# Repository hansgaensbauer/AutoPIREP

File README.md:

# AutoPIREP
AutoPIREP is a website, backend, and IOS app for automatically reporting turbulence in General Aviation flights. Traditionally, a pilot is expected to radio air traffic control to submit a Pilot Report (PIREP) when they encounter turbulence. The IOS app presented here uses the accelerometer in an iPhone to detect turbulence, and then submits reports to a custom backend running in AWS. The website displays the reports on a map for other pilots to reference.

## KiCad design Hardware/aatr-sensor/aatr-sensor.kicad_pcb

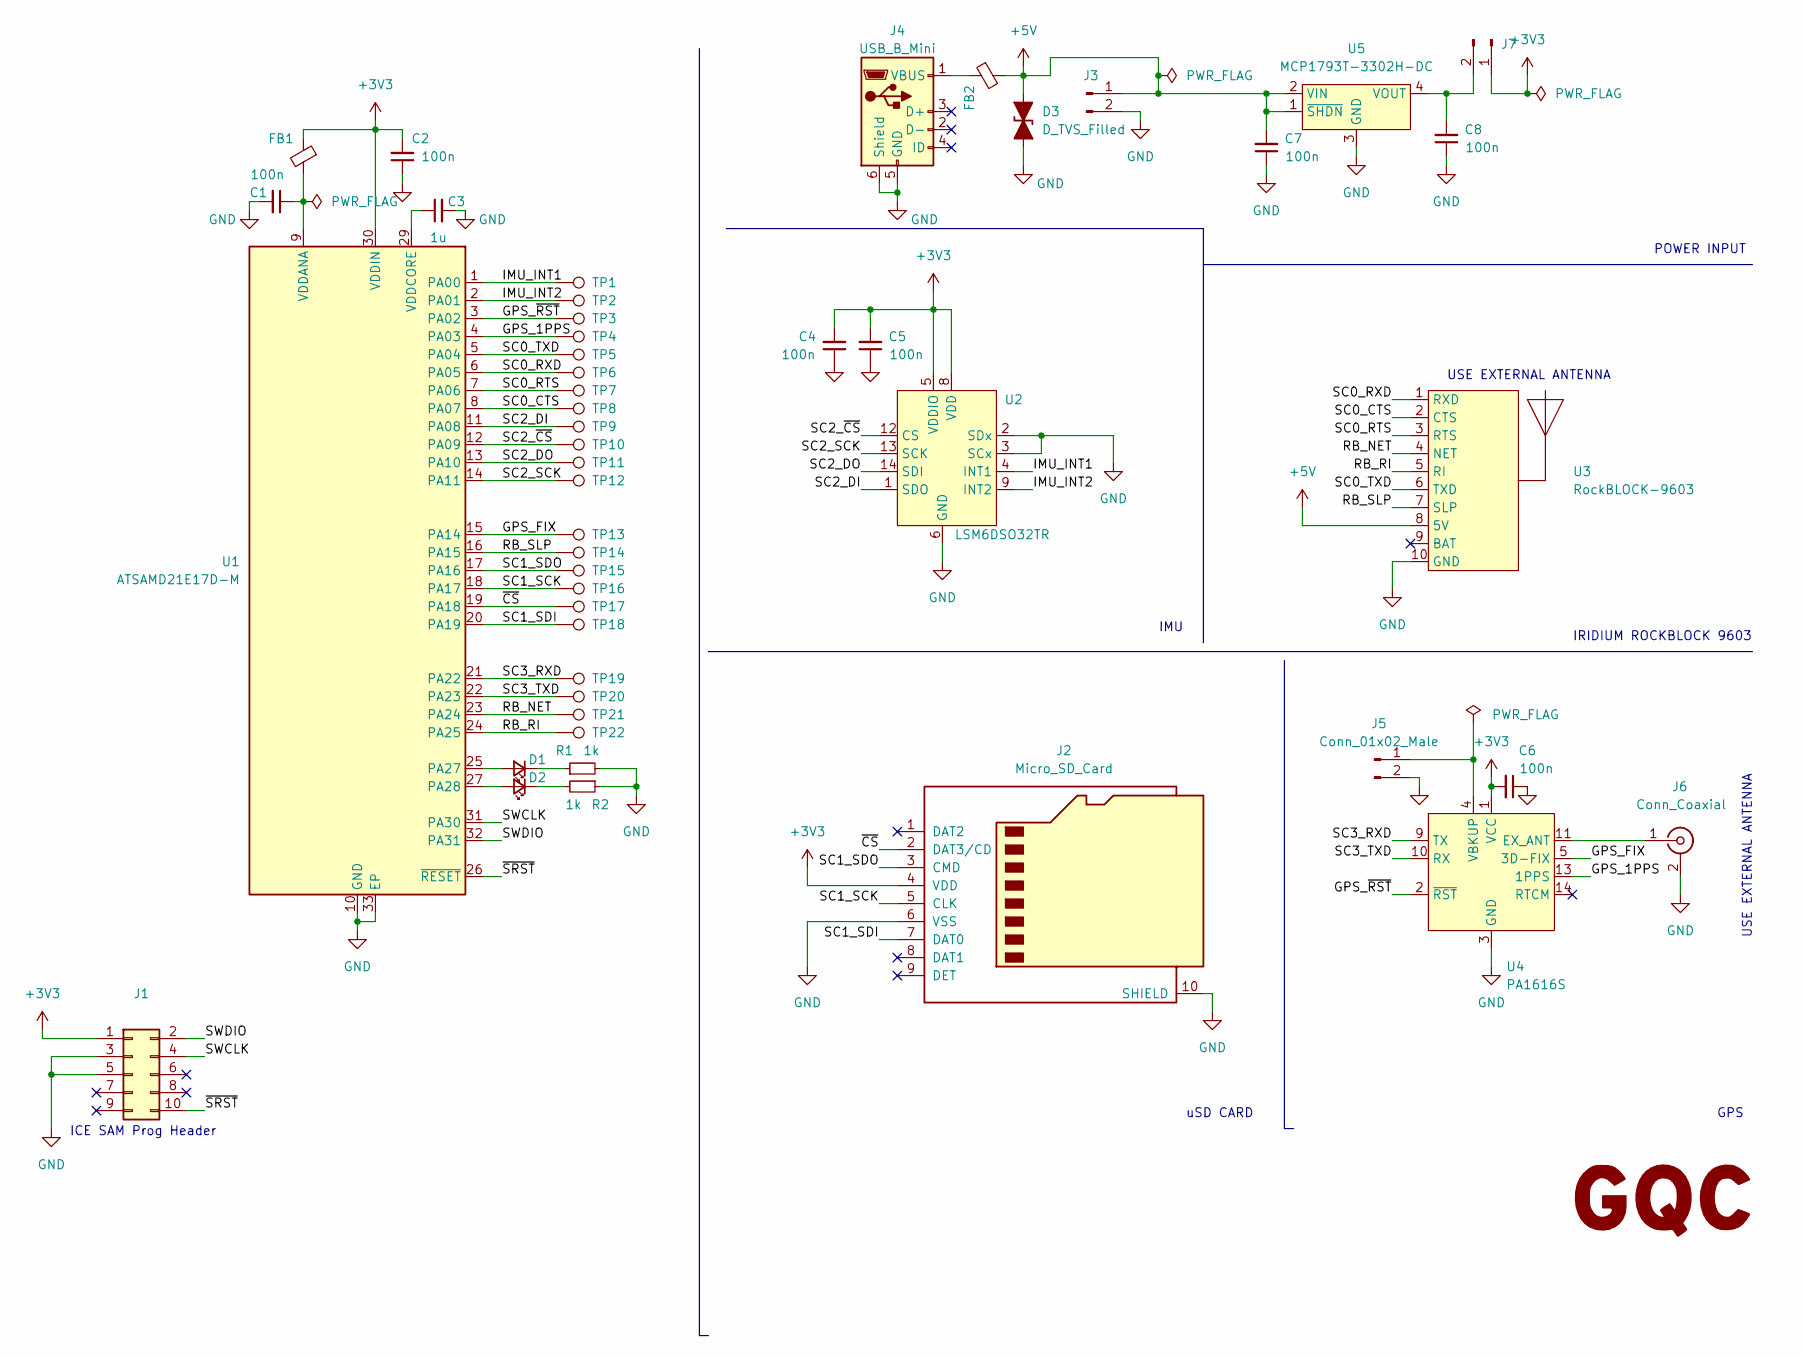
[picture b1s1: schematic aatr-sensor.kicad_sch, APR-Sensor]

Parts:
C1, C2, C4, C5, C6, C7, C8: 100n; C_0603_1608Metric
C3: 1u; C_0603_1608Metric
D1, D2: LED_Small; LED_0805_2012Metric
D3: D_TVS_Filled; D_0201_0603Metric
FB1, FB2: FerriteBead_Small; L_0603_1608Metric
G1: GQC-Logo
J1: Conn_02x05_Odd_Even; 3221-10-0300-00-TR
J2: Micro_SD_Card; MEM2051-00-195-00-A
J3, J5, J7: Conn_01x02_Male; PinHeader_1x02_P2.54mm_Vertical
J4: USB_B_Mini; USB_Mini-B_Wuerth_65100516121_Horizontal
J6: Conn_Coaxial; SMA_Samtec_SMA-J-P-X-ST-EM1_EdgeMount
R1, R2: 1k; R_0603_1608Metric
TP1, TP2, TP3, TP4, TP5, TP6, TP7, TP8, TP9, TP10, TP11, TP12, TP13, TP14, TP15, TP16, TP17, TP18, TP19, TP20, TP21, TP22: TestPoint; RCU-0603
U1: ATSAMD21E17D-M; QFN-32-1EP_5x5mm_P0.5mm_EP3.6x3.6mm
U2: LSM6DSO32TR; LGA-14_3x2.5mm_P0.5mm_LayoutBorder3x4y
U3: RockBLOCK-9603; Molex_PicoBlade_53047-1010_1x10_P1.25mm_Vertical
U4: PA1616S; FGPMMOPA6H
U5: MCP1793T-3302H-DC; SOT-223-6

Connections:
+3V3: C2.2, C4.2, C5.2, C6.2, FB1.1, J1.1, J2.4 (VDD), J7.1, U1.30 (VDDIN), U2.5 (VDDIO), U2.8 (VDD), U4.1 (VCC)
+5V: C7.2, D3.2 (A2), FB2.2, J3.1, U3.8 (5V), U5.1 (~SHDN), U5.2 (VIN)
/GPS_1PPS: TP4.1, U1.4 (PA03), U4.13 (1PPS)
/GPS_FIX: TP13.1, U1.15 (PA14), U4.5 (3D-FIX)
/GPS_~RST: TP3.1, U1.3 (PA02), U4.2 (~RST)
/IMU_INT1: TP1.1, U1.1 (PA00), U2.4 (INT1)
/IMU_INT2: TP2.1, U1.2 (PA01), U2.9 (INT2)
/RB_NET: TP21.1, U1.23 (PA24), U3.4 (NET)
/RB_RI: TP22.1, U1.24 (PA25), U3.5 (RI)
/RB_SLP: TP14.1, U1.16 (PA15), U3.7 (SLP)
/SC0_CTS: TP8.1, U1.8 (PA07), U3.2 (CTS)
/SC0_RTS: TP7.1, U1.7 (PA06), U3.3 (RTS)
/SC0_RXD: TP6.1, U1.6 (PA05), U3.1 (RXD)
/SC0_TXD: TP5.1, U1.5 (PA04), U3.6 (TXD)
/SC1_SCK: J2.5 (CLK), TP16.1, U1.18 (PA17)
/SC1_SDI: J2.7 (DAT0), TP18.1, U1.20 (PA19)
/SC1_SDO: J2.3 (CMD), TP15.1, U1.17 (PA16)
/SC2_DI: TP9.1, U1.11 (PA08), U2.1 (SDO)
/SC2_DO: TP11.1, U1.13 (PA10), U2.14 (SDI)
/SC2_SCK: TP12.1, U1.14 (PA11), U2.13 (SCK)
/SC2_~CS: TP10.1, U1.12 (PA09), U2.12 (CS)
/SC3_RXD: TP19.1, U1.21 (PA22), U4.9 (TX)
/SC3_TXD: TP20.1, U1.22 (PA23), U4.10 (RX)
/SWCLK: J1.4, U1.31 (PA30)
/SWDIO: J1.2, U1.32 (PA31)
/~CS: J2.2 (DAT3/CD), TP17.1, U1.19 (PA18)
/~SRST: J1.10, U1.26 (~RESET)
GND: C1.2, C2.1, C3.2, C4.1, C5.1, C6.1, C7.1, C8.1, D3.1 (A1), J1.3, J1.5, J2.6 (VSS), J2.10 (SHIELD), J3.2, J4.5 (GND), J4.6 (Shield), J5.2, J6.2 (Ext), R1.2, R2.1, U1.10 (GND), U1.28 (GND), U1.33 (EP), U2.2 (SDx), U2.3 (SCx), U2.6 (GND), U2.7 (GND), U3.10 (GND), U4. (GND), U4.3 (GND), U4.8 (GND), U4.12 (GND), U4.19 (GND), U5.3 (GND), U5.6 (GND)
unnamed: C1.1, FB1.2, U1.9 (VDDANA)
unnamed: C3.1, U1.29 (VDDCORE)
unnamed: C8.2, J7.2, U5.4 (VOUT)
unnamed: D1.1 (K), R1.1
unnamed: D1.2 (A), U1.25 (PA27)
unnamed: D2.1 (K), R2.2
unnamed: D2.2 (A), U1.27 (PA28)
unnamed: FB2.1, J4.1 (VBUS)
unnamed: J5.1, U4.4 (VBKUP)
unnamed: J6.1 (In), U4.11 (EX_ANT)

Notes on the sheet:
ICE SAM Prog Header
GPS
uSD CARD
IMU
USE EXTERNAL ANTENNA
IRIDIUM ROCKBLOCK 9603
POWER INPUT

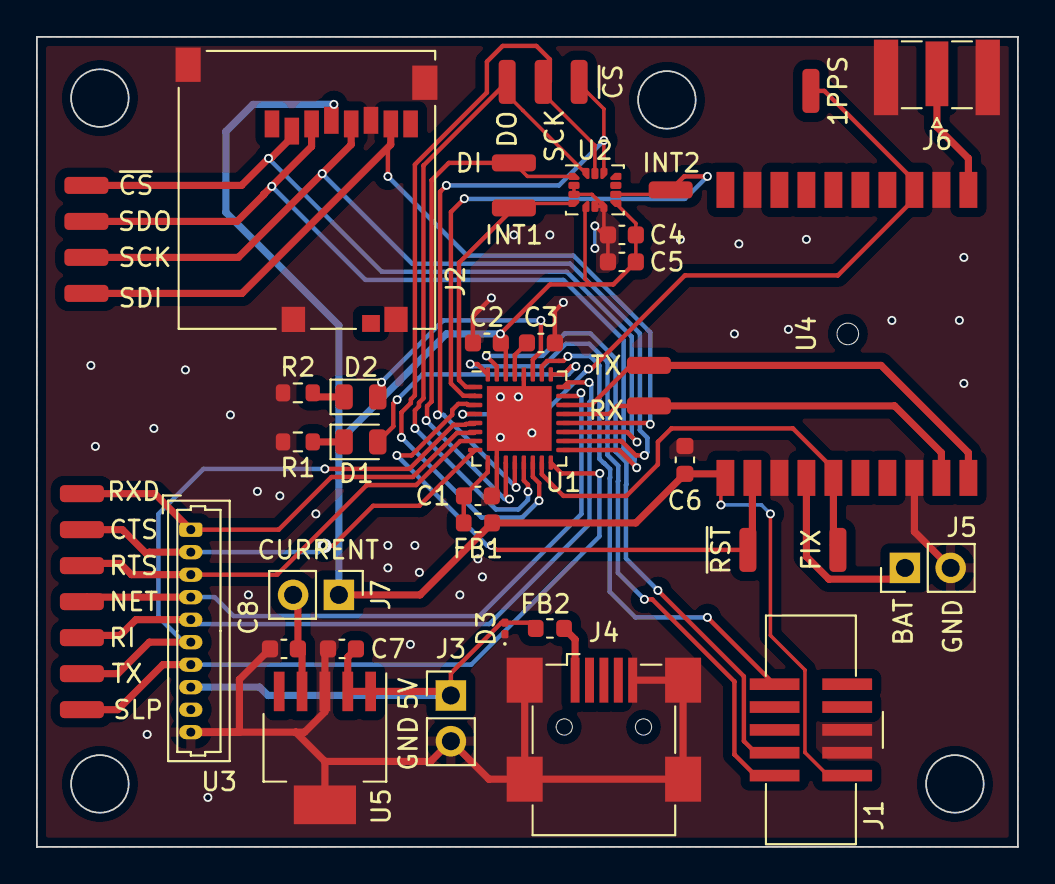
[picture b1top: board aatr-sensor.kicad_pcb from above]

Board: 2 copper layers, 54.5 x 45.0 mm, 50 parts (1 on the bottom side), 38 nets.

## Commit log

2022-05-03 Datalogger: Add firmware to remote
    Add the python files and bash scripts for setting up the RPi datalogger to the repo.
2022-05-23 APR-Sensor First Pass ERC Pass
2022-05-25 APR-Sensor Floorplanning
2022-05-26 AATR-Sensor: Create BOM, CAM Files
2022-05-26 AATR-Sensor: Remove Backups
2022-06-18 Update Science Names, add pdf Schematic
2022-06-18 Create Firmware Branch
    Created Microchip Studio project with ASF
2022-06-18 Add Documentation and AATR Image
2022-06-29 FW: ADD ASF Components
    Included SDMMC, FATFS, and delay drivers. Projects builds without errors.
2022-06-29 FW: SD log compiles
2022-06-29 FW: Added board init and error handlers
2022-07-03 FW: Debug SDMMC
2022-07-04 FW: Add UART Support
2022-07-06 FW: USART Works
2022-07-06 FW: Fix RX for USART
2022-07-06 FW: IMU SPI Driver Works
2022-07-06 FW: SPI Talks to IMU
2022-07-06 FW: SPI Debugging
2022-07-07 FW: Reading IMU Data
2022-07-07 FW: Fix IMU XL FS settings
2022-07-07 FW: SD Works!
2022-07-12 FW: Filling FIFO
2022-07-12 FW: Draft FIFO Read
2022-07-13 FW: FIFO Read 2 bit Error
2022-07-13 FW: Streaming IMU Data, Not Enough RAM
2022-07-13 FW: Writing .ned Files
2022-07-14 FW: Lowered datarate, streaming data
2022-07-15 FW: Fixed missing byte, check pipeline IMU->uC
2022-07-15 FW: Most Datalogger Bugs Ironed Out
2022-07-15 FW: Datalogger Pipeline Working [!]
2022-07-16 SW: Visualizer Plotting Time Domain
2022-07-26 Science: Add Cell Phone Data
    Also split up science folder into subfolders for different analyses
2022-07-26 Science: Remove .csv from .gitignore and add data files
2022-07-26 Science: Cell Phone Time Domain
2022-07-26 FW: Add Serial No. and LED Blink
2024-06-16 Change to iphone implementation
2024-06-22 Switch to NRL TAC
2024-06-30 Website working, preparing to switch map providers
2024-07-01 Switch Map
2024-07-02 Use only geohash
2024-07-02 Click to center tac region
2024-07-02 Fix tac boundaries
2024-07-07 Create IOS App
2024-07-07 Add white square to icon
2024-07-07 screen changing and acceleration
2024-07-13 Location Working
2024-07-13 DB Push Working
2024-07-13 Timestamp limits and zulu time
2024-07-26 App fixes and jitter
2024-08-11 Add science data and fix scrolling for Privacy Policy
2024-08-11 Keep severe markers on top
2024-08-11 Update symbol size after every zoom
2024-10-26 Add Screenshots
2025-05-01 Created using Colab

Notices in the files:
parts and their libraries:
Copyright 2021 Accelerated Designs. All rights reserved.
